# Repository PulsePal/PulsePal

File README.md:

PulsePal
========

Code and CAD for Pulse Pal

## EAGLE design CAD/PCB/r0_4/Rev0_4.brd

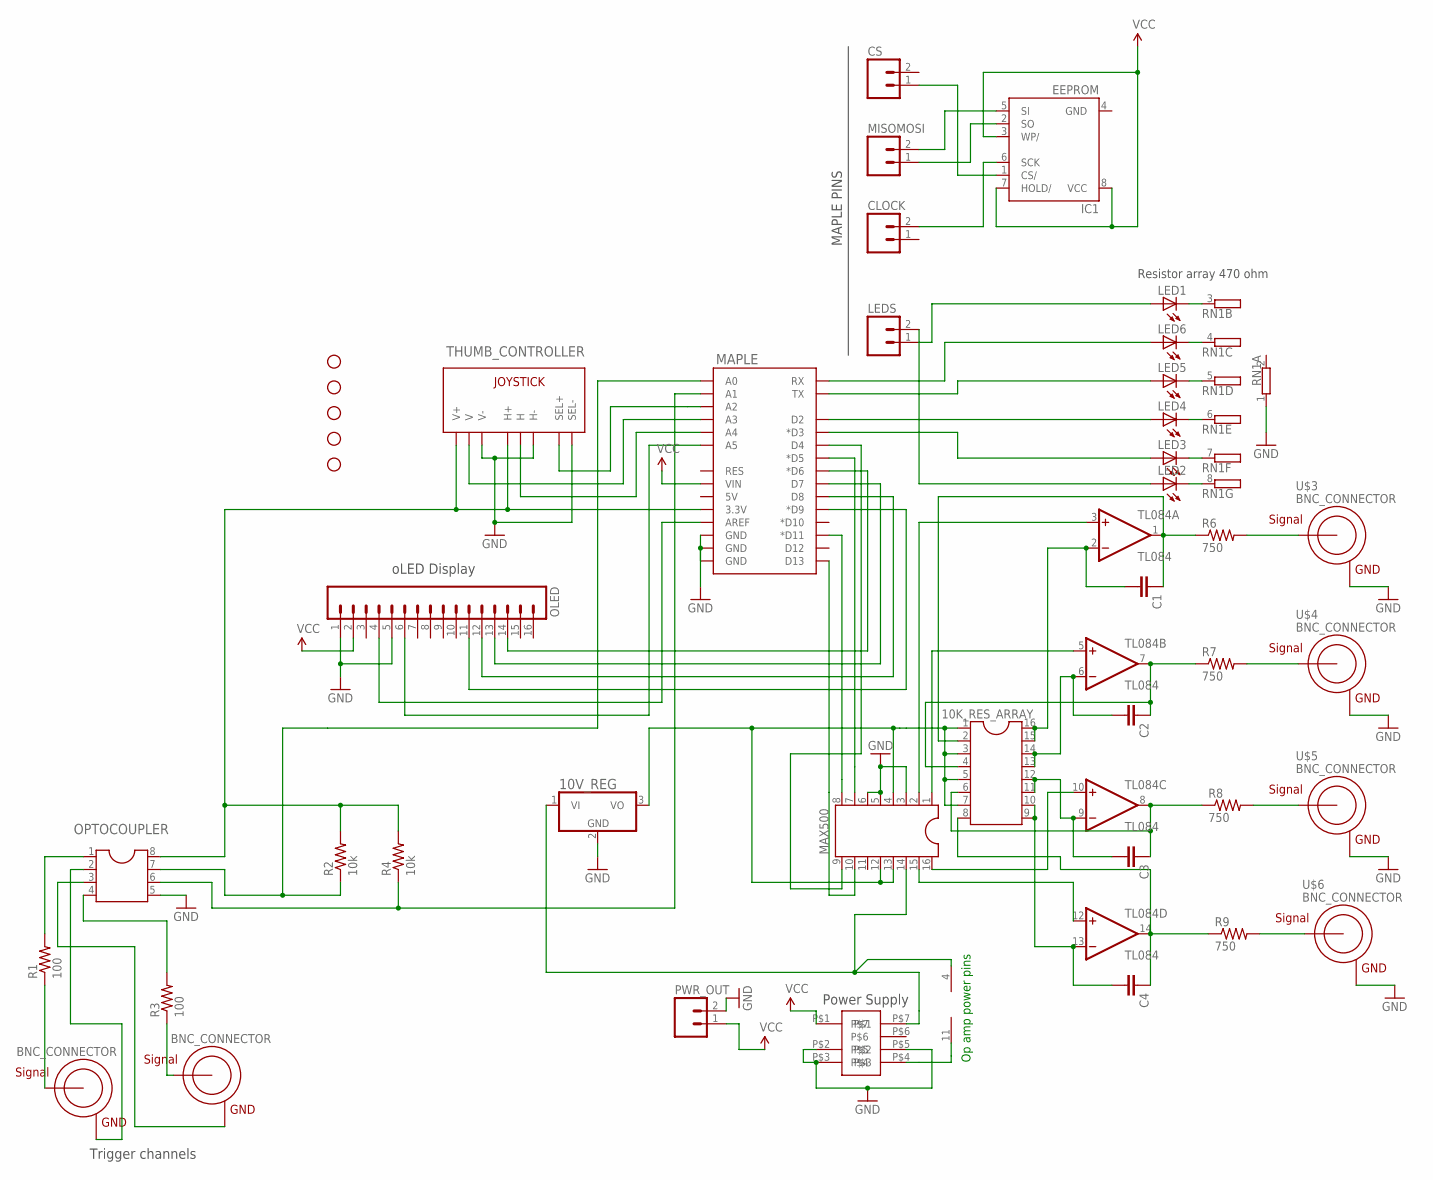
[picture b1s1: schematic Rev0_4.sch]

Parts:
10K_RES_ARRAY: DIL16
10V_REG: 7805T; TO220H
C1, C2, C3, C4: CAPPTH; CAP-PTH-SMALL
CLOCK: M02PTH; 1X02
CS: M02PTH; 1X02
IC1: EEPROM; DIL08
JP2, JP5, JP6, JP8, JP9: STAND-OFF
LED1, LED2, LED3, LED4, LED5, LED6: LED3MM
LEDS: M02PTH; 1X02
MAPLE: ARDUINO_SHIELDNOHOLESORLABELS; DUEMILANOVE_SHIELD_NOHOLES_NOLABELS
MAX500: DIL16
MISOMOSI: M02PTH; 1X02
OLED: M16PTH; 1X16
OPTOCOUPLER: DIL8; DIL08
PWR_OUT: M02PTH; 1X02
R1, R3: 100; AXIAL-0.3
R2, R4: 10k; AXIAL-0.3
R6, R7, R8, R9: 750; AXIAL-0.3
RN1: GE07R; SIL8
THUMB_CONTROLLER: JOYSTICKPTH; JOYSTICK
TL084: TL084; DIL14
U$1, U$2, U$3, U$4, U$5, U$6: BNC_CONNECTOR
U$8: TDK_LAMBDA_5_TO_BI_12_125MA

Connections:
GND: 10V_REG.2 (GND), IC1.4 (GND), MAPLE.GND@0 (GND), MAPLE.GND@1 (GND), MAPLE.GND@2 (GND), MAX500.3, MAX500.5, MAX500.6, OLED.1, OLED.5, OPTOCOUPLER.5, PWR_OUT.2, RN1.1, THUMB_CONTROLLER.B2A (SEL-), THUMB_CONTROLLER.H3 (H-), THUMB_CONTROLLER.V3 (V-), U$3.GND, U$4.GND, U$5.GND, U$6.GND, U$8.P$2, U$8.P$3, U$8.P$5
unnamed: LED6.A, MAPLE.RX
unnamed: LED5.A, MAPLE.TX
unnamed: LED4.A, MAPLE.D2
unnamed: LED3.A, MAPLE.D3 (*D3)
unnamed: MAPLE.D11 (*D11), MAX500.8
unnamed: MAPLE.D13, MAX500.10
unnamed: MAPLE.AREF, OLED.4
unnamed: MAPLE.D4, MAX500.9
unnamed: MAPLE.D5 (*D5), MAX500.7
unnamed: MAPLE.D6 (*D6), OLED.14
unnamed: MAPLE.D7, OLED.13
unnamed: MAPLE.D8, OLED.12
unnamed: MAPLE.D9 (*D9), OLED.11
unnamed: MAPLE.A5, OLED.6
unnamed: MAPLE.A4, THUMB_CONTROLLER.H2 (H)
unnamed: MAPLE.A3, THUMB_CONTROLLER.V2 (V)
unnamed: MAPLE.A2, THUMB_CONTROLLER.B1A (SEL+)
unnamed: R1.P$1 (1), U$1.SIGNAL
unnamed: MAPLE.A0, OPTOCOUPLER.7, R2.P$1 (1)
unnamed: R3.P$1 (1), U$2.SIGNAL
unnamed: MAPLE.A1, OPTOCOUPLER.6, R4.P$1 (1)
unnamed: TL084.11 (V-), U$8.P$4
unnamed: MAX500.2, TL084.3 (+IN)
unnamed: MAX500.1, TL084.5 (+IN)
unnamed: 10V_REG.1 (VI), MAX500.14, TL084.4 (V+), U$8.P$7
unnamed: 10K_RES_ARRAY.1, 10K_RES_ARRAY.3, 10K_RES_ARRAY.5, 10K_RES_ARRAY.7, 10V_REG.3 (VO), MAX500.4, MAX500.12, MAX500.13
unnamed: MAX500.16, TL084.10 (+IN)
unnamed: MAX500.15, TL084.12 (+IN)
unnamed: 10K_RES_ARRAY.2, C1.1, R6.P$1 (1), TL084.1 (OUT)
unnamed: 10K_RES_ARRAY.4, C2.1, R7.P$1 (1), TL084.7 (OUT)
unnamed: 10K_RES_ARRAY.6, C3.1, R8.P$1 (1), TL084.8 (OUT)
unnamed: 10K_RES_ARRAY.8, C4.1, R9.P$1 (1), TL084.14 (OUT)
unnamed: LED1.A, LEDS.1
unnamed: LED2.A, LEDS.2
unnamed: LED2.K (C), RN1.8 (2)
unnamed: LED3.K (C), RN1.7 (2)
unnamed: LED4.K (C), RN1.6 (2)
unnamed: LED5.K (C), RN1.5 (2)
unnamed: LED6.K (C), RN1.4 (2)
unnamed: 10K_RES_ARRAY.15, 10K_RES_ARRAY.16, C1.2, TL084.2 (-IN)
unnamed: 10K_RES_ARRAY.13, 10K_RES_ARRAY.14, C2.2, TL084.6 (-IN)
unnamed: 10K_RES_ARRAY.11, 10K_RES_ARRAY.12, C3.2, TL084.9 (-IN)
unnamed: 10K_RES_ARRAY.9, 10K_RES_ARRAY.10, C4.2, TL084.13 (-IN)
unnamed: LED1.K (C), RN1.3 (2)
unnamed: R6.P$2 (2), U$3.SIGNAL
unnamed: R7.P$2 (2), U$4.SIGNAL
unnamed: R8.P$2 (2), U$5.SIGNAL
unnamed: R9.P$2 (2), U$6.SIGNAL
unnamed: OPTOCOUPLER.1, R1.P$2 (2)
unnamed: CS.1, IC1.1 (CS/)
unnamed: IC1.5 (SI), MISOMOSI.2
unnamed: IC1.2 (SO), MISOMOSI.1
unnamed: CLOCK.2, IC1.6 (SCK)
unnamed: OPTOCOUPLER.2, U$1.GND
unnamed: OPTOCOUPLER.4, R3.P$2 (2)
unnamed: OPTOCOUPLER.3, U$2.GND
unnamed: MAPLE.3.3V, OPTOCOUPLER.8, R2.P$2 (2), R4.P$2 (2), THUMB_CONTROLLER.H1 (H+), THUMB_CONTROLLER.V1 (V+)
VCC: IC1.3 (WP/), IC1.7 (HOLD/), IC1.8 (VCC), MAPLE.VIN, OLED.2, PWR_OUT.1, U$8.P$1

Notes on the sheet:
oLED Display
Power Supply
Op amp power pins
MAPLE PINS
Trigger channels
Resistor array 470 ohm

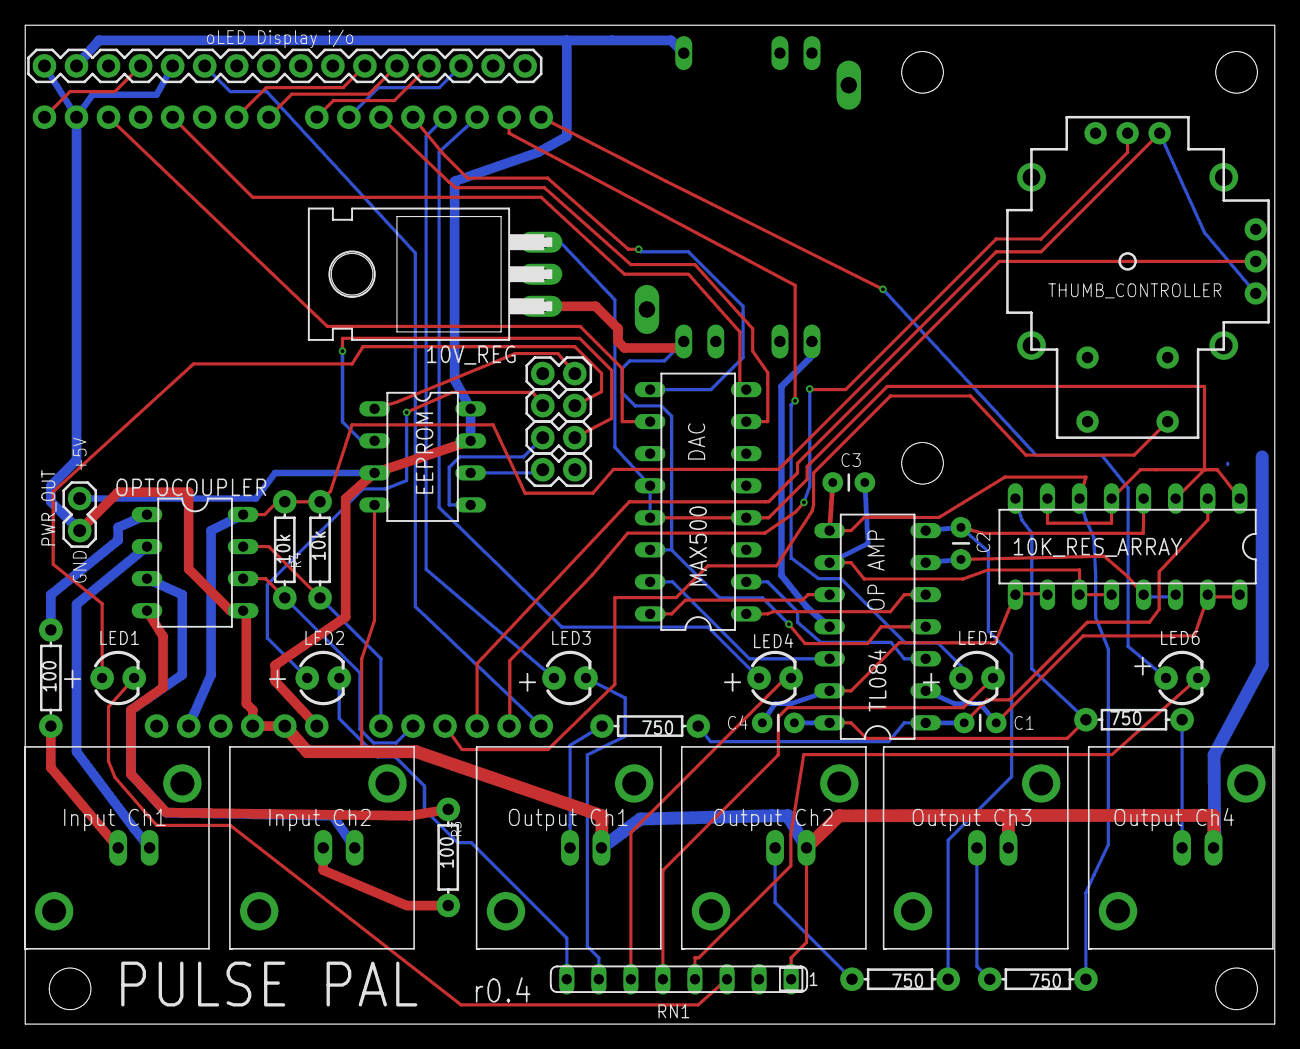
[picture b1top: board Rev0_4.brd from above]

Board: 4 copper layers, 99.0 x 79.2 mm, 45 parts (1 on the bottom side), 59 nets.

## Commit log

2014-01-29 Reorganized media folders
2014-01-30 -Added firmware version to handshake (in firmware and MATLAB client) -Updated firmware terms for trigger channels and custom trains to match terms in client and wiki
2014-01-30 -Converted channel indexing so that the shift to zero happens on the pulse pal firmware end, and software clients can be more intuitive. -Modified PulsePalDisplay on both ends so reading strings is r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
2014-02-04 -Added pulse-gate functionality to trigger channels -Added new c++ API (tested, working) -Made parameter names in MATLAB, firmware and c++ consistent with parameter names on wiki. -Partially solved c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
2014-02-04 -Fixed custom pulse train bug causing short first pulse. -Bug: First pulse of custom loop is still 50us
2014-02-04 -Fixed first pulse of custom loop problem by setting Pulse Pal's cycle duration to 100us instead of 50us. -Added parameter in MATLAB client, which uses firmware version returned during handshake to d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
2014-02-04 Formatted c++ API for alpha deployment Fixed a GUI bug
2014-02-06 -Added firmware fork for r0.2 -Placed op code after sanity checks in SendCustomPulseTrain -Made Sleep macro for unix in PulsePal.cpp
2014-02-06 Removed requirement that custom pulse times be multiples of the minimum cycle. This allows continuous values to be sent, and automatically mapped to the nearest cycle.
2014-02-10 Added firmware fork for r0.3
2014-02-10 Fixed code to launch online help documentation from MATLAB GUI - used system's default browser instead of MATLAB browser since google docs has a security certificate
2014-02-10 Fixed version numbers in 0_2 and 0_3 firmware Fixed precision limit for joystick time parameter entry in 0_2 and 0_3 firmware
2014-02-13 -Added license to each script -Updated syntax for sending custom pulse trains in C++ API to match MATLAB API -Added revised PCB design files to account for longer op amp package (TI replaces ST micro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
2014-02-14 Added Python API
2014-02-18 Top level of thumb joystick menu is now application-configurable (used to be hard-coded as "MATLAB" in firmware) Minor mod to firmware to economize memory Disconnected top-level joystick menu now sho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
2014-02-21 -Renamed "programAllParams" function to "syncAllParams", reflecting the fact that this function reads all params from the object fields instead of them being passed explicitly
2014-02-26 Added pre-zipped GERBER for easy PCB ordering Added a MATLAB convenience function to make sine waves in phase, for custom waveform looping
2014-03-06 Changed output channel series resistors in CAD files from 1k to 750-ohm (current-limits outputs to a max of 10mA, previously 8.6mA)
2014-03-08 In python client, changed "line" to "row" for convention in setDisplay function
2014-03-14 Adds a hard reset function to the thumb joystick menu. This causes a power-cycle. -Useful for cases where the governing computer crashes during parameter transmission and Pulse Pal loops, waiting for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
2014-03-14 Fixes menu wrap limits for thumb joystick menu, to accomodate new reset function. Updated menu-map graphic.
2014-03-14 Updated reset menu text
2014-03-14 Replaced bipolar voltage converter in PCB design (and BOM) with a lower power, lower cost, more available part from the same family.
2014-03-26 - Set MATLAB com port auto-detect in Windows XP Home edition to throw an error - Added a dedicated COM port option to the MATLAB client (i.e. PulsePal('COM3'): tries on COM3, while PulsePal; auto-det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
2014-03-27 Added serial read timeout support to v0.4 firmware. Previously, if a transmission started and failed on the computer end, Pulse Pal would wait indefinitely for data. Starting with this update, Pulse 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
2014-03-27 -Added license text to firmware -Added serial timeout support in firmware r0.3
2014-03-31 -Cleaned up schematic (preliminary - final version will require re-routing the board)
2014-04-01 Since update to CC3-0512DF-E voltage converter, schematic contained an air-wire. This is now routed. Added schematic graphic of essential circuit for reading triggers and generating outputs.
2014-04-02 Firmware for r0.4 devices: Added thumb joystick menu support for programming and soft-triggering the trigger channels. (Trigger channels were previously shown on the top level menu, but were inaccess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
2014-04-15 Added timeout support in firmware for r0.3 Fixed rounding bug in MATLAB single parameter update command (affects MATLAB r2009a)
2014-04-28 Optimized timing system to count multiples of complete main loop cycles instead of microseconds. Requires firmware and software client updates.
2014-04-30 Modified MATLAB GUI units to pixels for cross-platform compatability Minor syntax fixes in GUI background image
2014-05-01 Fixed serial transmission bugs in MATLAB API, affecting transmission of custom pulse trains on OS X and Win XP
2014-05-06 Modified 0_4 firmware to achieve a ~50us improvement in post-trigger stimulus latency by skipping cycle uniformity delay loop when not actively stimulating. Latency is now 50-80us.
2014-05-14 -Fixed voltage to byte conversion in c++ and python clients -Added RestingVoltage parameter for output channels - the voltage between phases, pulses and trains (previously fixed at 0V). This change a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
2014-05-16 Modified firmware to use hardware timer for cycle timing. Marked reduction of cycle jitter.
2014-05-16 - Fixed bug with hard-triggering custom trains of bursts - In MATLAB client, forced monophasic pulses when sending a waveform.
2014-05-18 Extended previous firmware update to r0.3
2014-05-21 -Fixed a bug introduced with new hardware timing scheme in a previous update (reduces jitter in first pulse after trigger). -Fixed COM port auto-detect and GUI layout in MATLAB, for Ubuntu 14
2014-05-21 Added an "Op menu byte (=213)" before each serial transmission, to reduce interference from user apps that spam serial ports. This especially helps with Ubuntu 14, which spams the port by default wit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
2014-05-22 -Reduced clock drift to 0.00002s / 10s with respect to NI acquisition card, by directly setting timer prescale and overflow instead of leaflabs "timer period" function (apparently broken?) -Timer no 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
2014-06-11 Fixed bug introduced with new timing scheme - if set by thumb joystick, time values were capped at only half of their intended range. Fixed so they once again range between 100us and 3600s.
2014-06-18 -Changed repository name to PulsePal 1_0, reflecting the first post-beta hardware design. -Added new circuit design file for version 1.0. (Improved ground plane, removed unnecessary resistors on outp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
2014-06-18 -Updated enclosure engraving to v1.0 -Modified contour of rack mount wing
2014-07-17 Fixed firmware version - firmware now reports correct version number. Added dedicated folder with firmware used for precision and reliability measures in the Pulse Pal publication
2014-07-25 Removed stray trace from PCB layout
2014-07-30 Bug fix (in firmware): When Pulse Gated or TTL Toggle mode is used to stop stimulation during a pulse (instead of an interval), the linked output channels didn't return to their resting voltages. Wit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
2014-07-30 Fixed initialization for version 1.0 ProgramPulsePalParam function in MATLAB client fixed - now checks proper range of valid param codes
2014-08-07 -Under Windows XP, COM port auto-detect fails, possibly due to a different WMI command syntax. This update prompts the user to use the optional COM port argument when the OS is detected to be Win XP.
2014-08-28 -Updated default parameters in firmware, to load when EEPROM has not been written to (on first run): Resting Voltage = 0V (was previously -10V). Only updated this for r1.0; all new devices should be 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
2014-10-27 Added GERBER files for PCB fabrication with OSH Park
2015-02-12 Removed old circuit design from CAD folder
2015-03-03 Updated Maple drivers folder. The drivers folder now includes install_drivers.bat, an app that automatically installs Pulse Pal's Maple drivers in Windows 7, 8 and 8.1.
2015-03-18 Added automatic java.opts file configuration for MATLAB client under Ubuntu 14.04.
2015-03-18 Added GUI fix for MATLAB/Linux
